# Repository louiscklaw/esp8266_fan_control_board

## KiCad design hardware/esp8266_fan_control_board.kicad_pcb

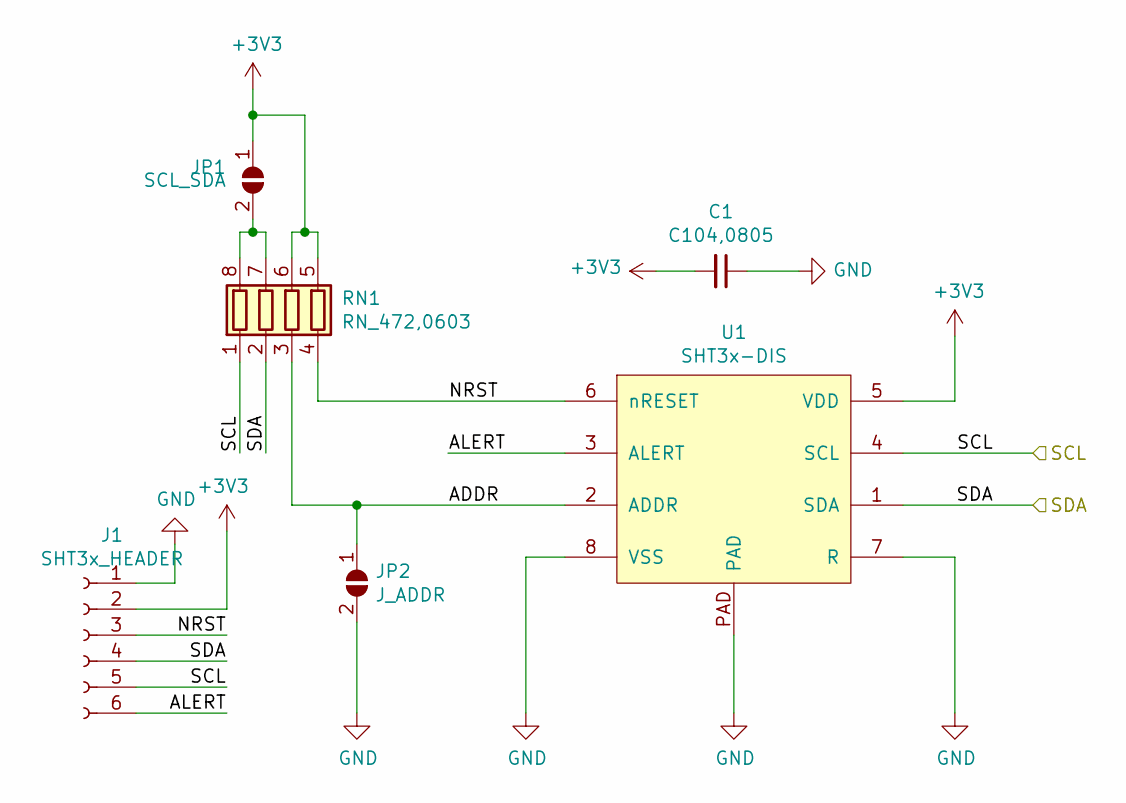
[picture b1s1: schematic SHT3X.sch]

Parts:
C1: C104,0805; C_0805_2012Metric_Pad1.15x1.40mm_HandSolder
J1: SHT3x_HEADER; PinHeader_1x06_P1.27mm_Vertical
JP1: SCL_SDA; SolderJumper-2_P1.3mm_Open_RoundedPad1.0x1.5mm
JP2: J_ADDR; SolderJumper-2_P1.3mm_Open_RoundedPad1.0x1.5mm
RN1: RN_472,0603; R_Array_Concave_4x0603
U1: SHT3x-DIS

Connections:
+3V3: C1.2, J1.2, JP1.1 (A), RN1.5 (R4.2), RN1.6 (R3.2), U1.5 (VDD); also elsewhere on the board
/SCL: J1.5, RN1.1 (R1.1), U1.4 (SCL); also elsewhere on the board
/SDA: J1.4, RN1.2 (R2.1), U1.1 (SDA); also elsewhere on the board
/SHT3X/ADDR: JP2.1 (A), RN1.3 (R3.1), U1.2 (ADDR)
/SHT3X/ALERT: J1.6, U1.3 (ALERT)
/SHT3X/NRST: J1.3, RN1.4 (R4.1), U1.6 (nRESET)
GND: C1.1, J1.1, JP2.2 (B), U1.7 (R), U1.8 (VSS), U1.PAD; also elsewhere on the board
unnamed: JP1.2 (B), RN1.7 (R2.2), RN1.8 (R1.2)

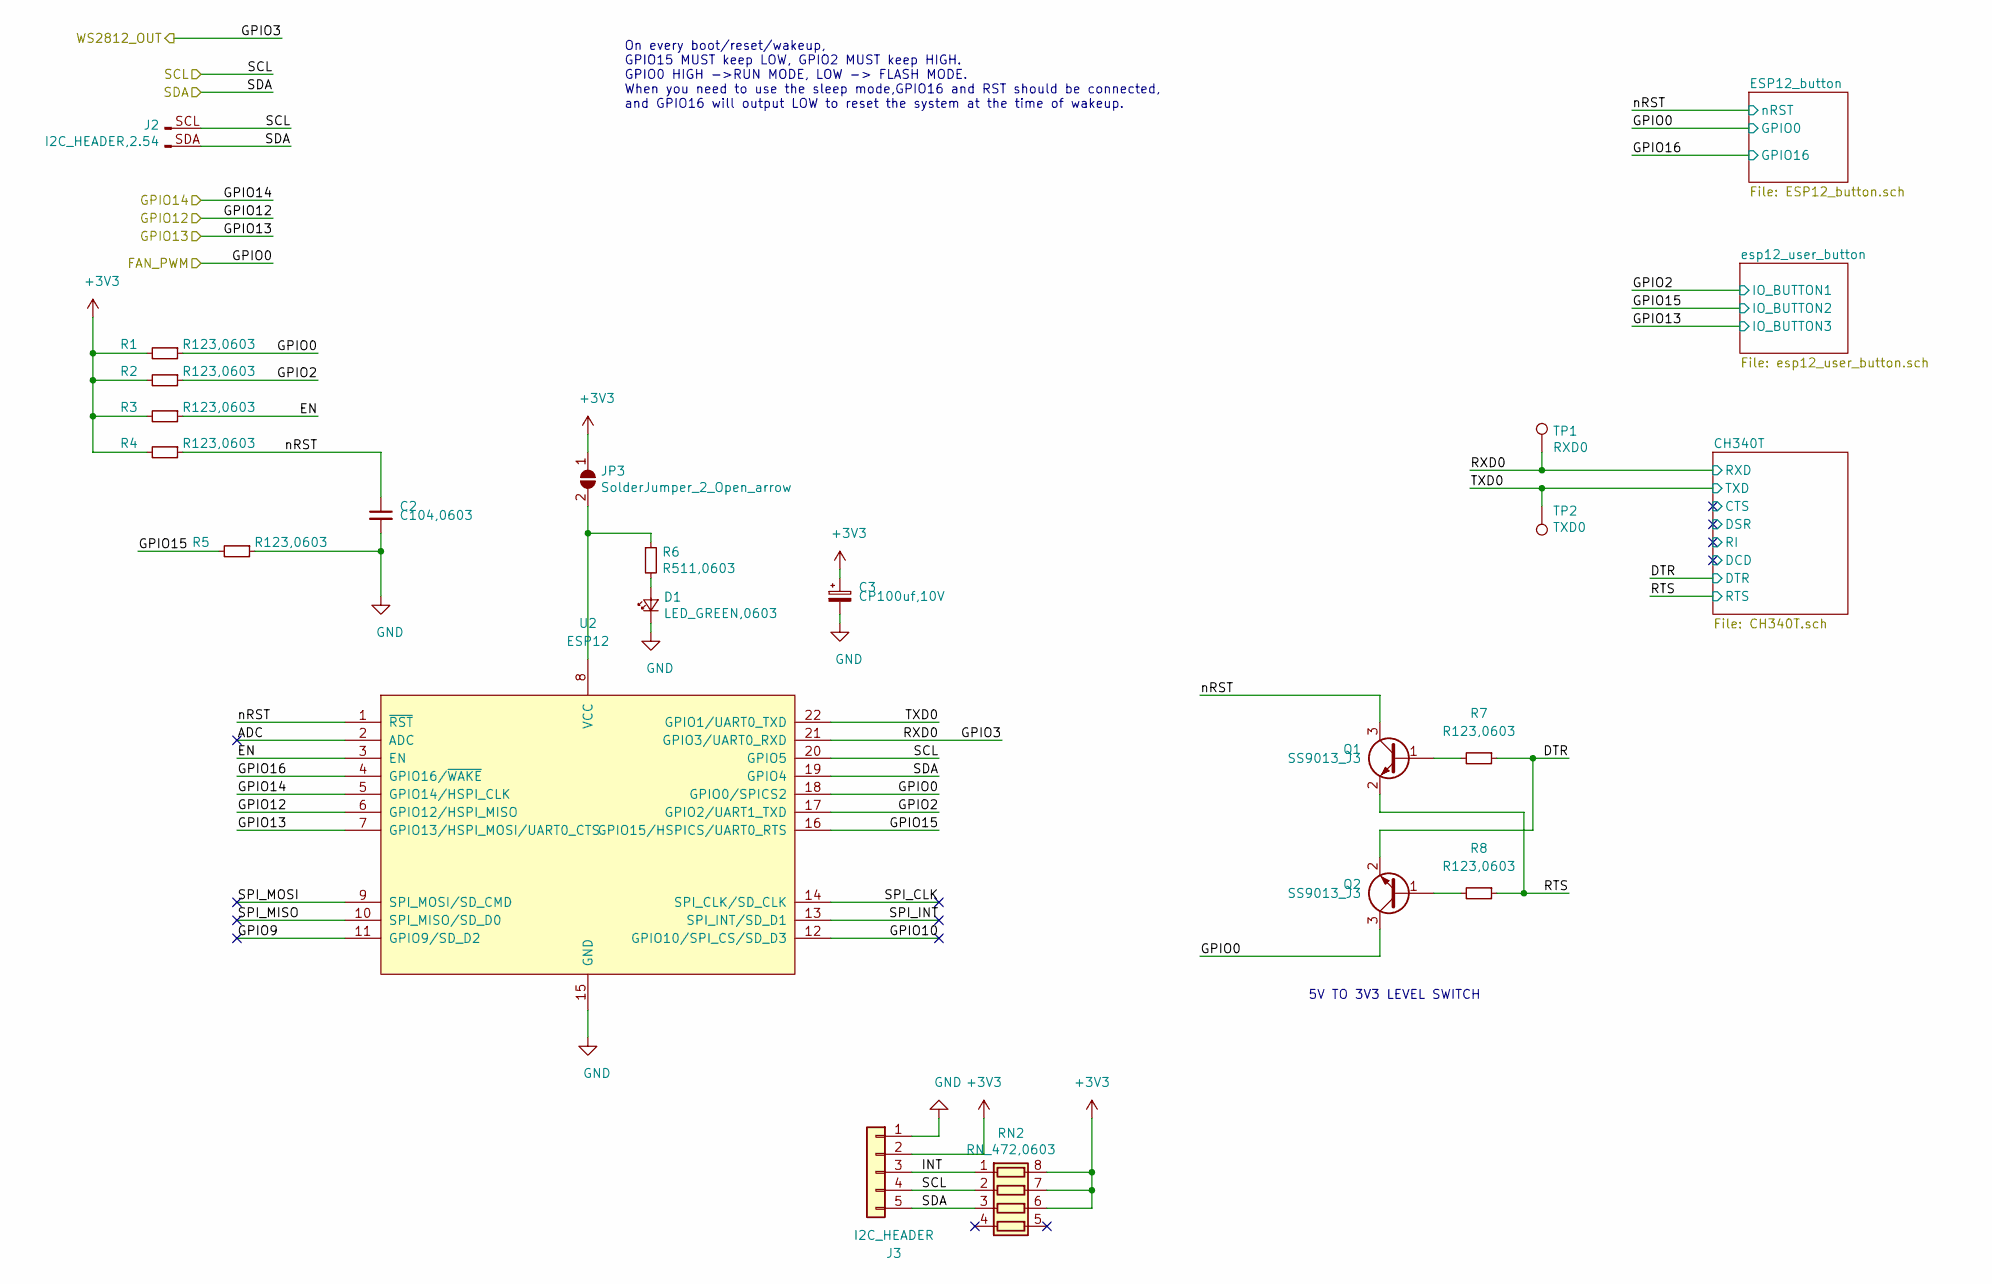
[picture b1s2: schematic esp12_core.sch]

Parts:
C2: C104,0603; C_0603_1608Metric_Pad1.05x0.95mm_HandSolder
C3: CP100uf,10V; CP_Elec_6.3x5.3
D1: LED_GREEN,0603; LED_0603_1608Metric
J2: I2C_HEADER,2.54; I2C_DEBUG,2.54
J3: I2C_HEADER; PinHeader_1x05_P2.54mm_Vertical
JP3: SolderJumper_2_Open_arrow; SolderJumper-2_P1.3mm_Open_TrianglePad1.0x1.5mm
Q1, Q2: SS9013_J3; 9013,J3,SOT23
R1, R2, R3, R4, R5, R7, R8: R123,0603; R_0603_1608Metric_Pad1.05x0.95mm_HandSolder
R6: R511,0603; R_0603_1608Metric_Pad1.05x0.95mm_HandSolder
RN2: RN_472,0603; R_Array_Concave_4x0603
TP1: RXD0; TestPoint_Pad_D1.0mm
TP2: TXD0; TestPoint_Pad_D1.0mm
U2: ESP12; ESP-12E

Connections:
+3V3: C3.1, J3.2, JP3.1 (A), R1.2, R2.2, R3.2, R4.2, RN2.6 (R3.2), RN2.7 (R2.2), RN2.8 (R1.2); also elsewhere on the board
/FAN0: Q2.3 (C), R1.1, U2.18 (GPIO0/SPICS2); also elsewhere on the board
/SCL: J2.SCL, J3.4, RN2.2 (R2.1), U2.20 (GPIO5); also elsewhere on the board
/SDA: J2.SDA, J3.5, RN2.3 (R3.1), U2.19 (GPIO4); also elsewhere on the board
/WS2812/WS2812_IN: TP1.1, U2.21 (GPIO3/UART0_RXD); also elsewhere on the board
/esp12_core/ADC: U2.2 (ADC)
/esp12_core/DTR: Q2.2 (E), R7.1; also elsewhere on the board
/esp12_core/EN: R3.1, U2.3 (EN)
/esp12_core/GPIO2: R2.1, U2.17 (GPIO2/UART1_TXD); also elsewhere on the board
/esp12_core/GPIO9: U2.11 (GPIO9/SD_D2)
/esp12_core/GPIO10: U2.12 (GPIO10/SPI_CS/SD_D3)
/esp12_core/GPIO14: U2.5 (GPIO14/HSPI_CLK); also elsewhere on the board
/esp12_core/GPIO15: R5.2, U2.16 (GPIO15/HSPICS/UART0_RTS); also elsewhere on the board
/esp12_core/GPIO16: U2.4 (GPIO16/~WAKE~); also elsewhere on the board
/esp12_core/INT: J3.3, RN2.1 (R1.1)
/esp12_core/RTS: Q1.2 (E), R8.1; also elsewhere on the board
/esp12_core/SPI_CLK: U2.14 (SPI_CLK/SD_CLK)
/esp12_core/SPI_INT: U2.13 (SPI_INT/SD_D1)
/esp12_core/SPI_MISO: U2.10 (SPI_MISO/SD_D0)
/esp12_core/SPI_MOSI: U2.9 (SPI_MOSI/SD_CMD)
/esp12_core/TXD0: TP2.1, U2.22 (GPIO1/UART0_TXD); also elsewhere on the board
/esp12_core/nRST: C2.1, Q1.3 (C), R4.1, U2.1 (~RST~); also elsewhere on the board
/rotary_encoder/A: U2.7 (GPIO13/HSPI_MOSI/UART0_CTS); also elsewhere on the board
/rotary_encoder/B: U2.6 (GPIO12/HSPI_MISO); also elsewhere on the board
GND: C2.2, C3.2, D1.1 (K), J3.1, R5.1, U2.15 (GND); also elsewhere on the board
unnamed: D1.2 (A), R6.2
unnamed: JP3.2 (B), R6.1, U2.8 (VCC)
unnamed: Q1.1 (B), R7.2
unnamed: Q2.1 (B), R8.2

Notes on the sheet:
On every boot/reset/wakeup, GPIO15 MUST keep LOW, GPIO2 MUST keep HIGH. GPIO0 HIGH ->RUN MODE, LOW -> FLASH MODE. When you need to use the sleep mode,GPIO16 and RST should be connected, and GPIO16 will output LOW to reset the system at the time of wakeup.
5V TO 3V3 LEVEL SWITCH

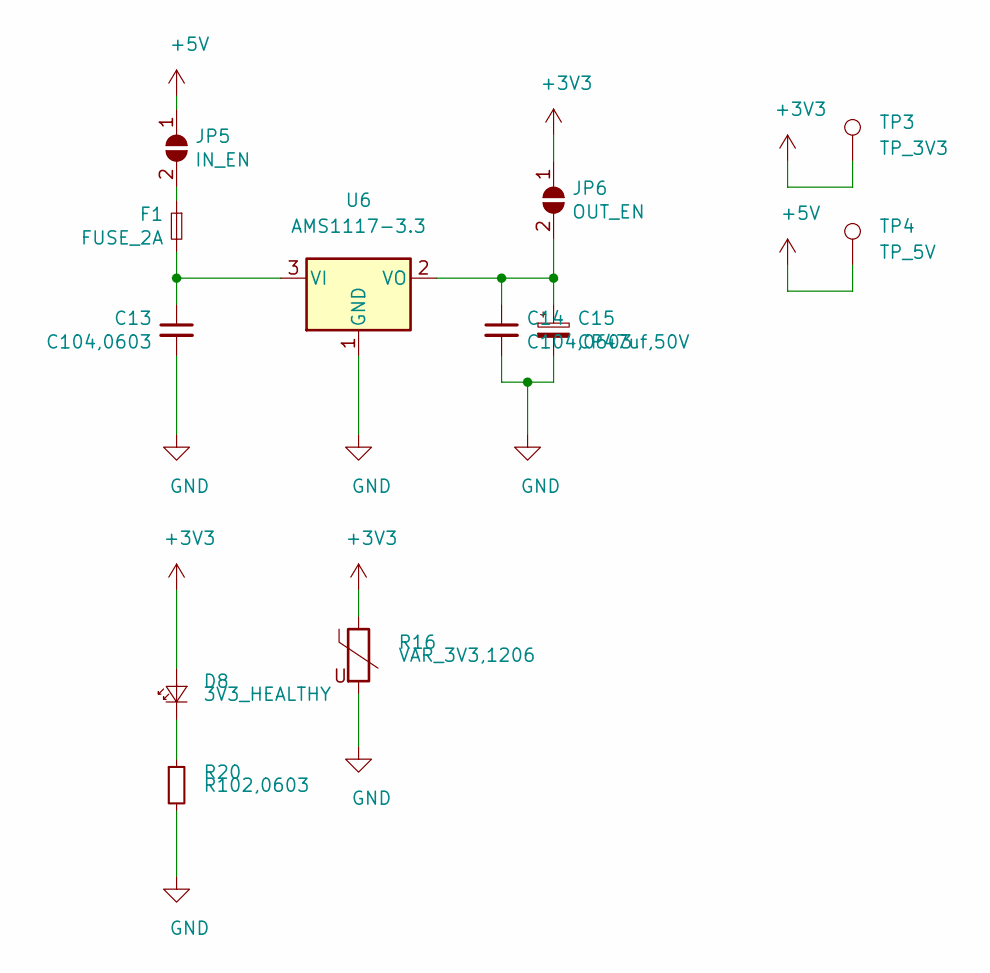
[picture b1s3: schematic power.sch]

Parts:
C13, C14: C104,0603; C_0603_1608Metric_Pad1.05x0.95mm_HandSolder
C15: CP47uf,50V; c_elec_6.3x7.7
D8: 3V3_HEALTHY; LED_0603_1608Metric_Pad1.05x0.95mm_HandSolder
F1: FUSE_2A; r_1210
JP5: IN_EN; SolderJumper-2_P1.3mm_Open_RoundedPad1.0x1.5mm
JP6: OUT_EN; SolderJumper-2_P1.3mm_Open_RoundedPad1.0x1.5mm
R16: VAR_3V3,1206; VAR_1206
R20: R102,0603; R_0603_1608Metric_Pad1.05x0.95mm_HandSolder
TP3: TP_3V3; Pin_D1.0mm_L10.0mm
TP4: TP_5V; Pin_D1.0mm_L10.0mm
U6: AMS1117-3.3; SOT-223-3_TabPin2

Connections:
+3V3: D8.2 (A), JP6.1 (A), R16.1, TP3.1; also elsewhere on the board
+5V: JP5.1 (A), TP4.1; also elsewhere on the board
GND: C13.2, C14.2, C15.2, R16.2, R20.2, U6.1 (GND); also elsewhere on the board
unnamed: C13.1, F1.2, U6.3 (VI)
unnamed: C14.1, C15.1, JP6.2 (B), U6.2 (VO)
unnamed: D8.1 (K), R20.1
unnamed: F1.1, JP5.2 (B)

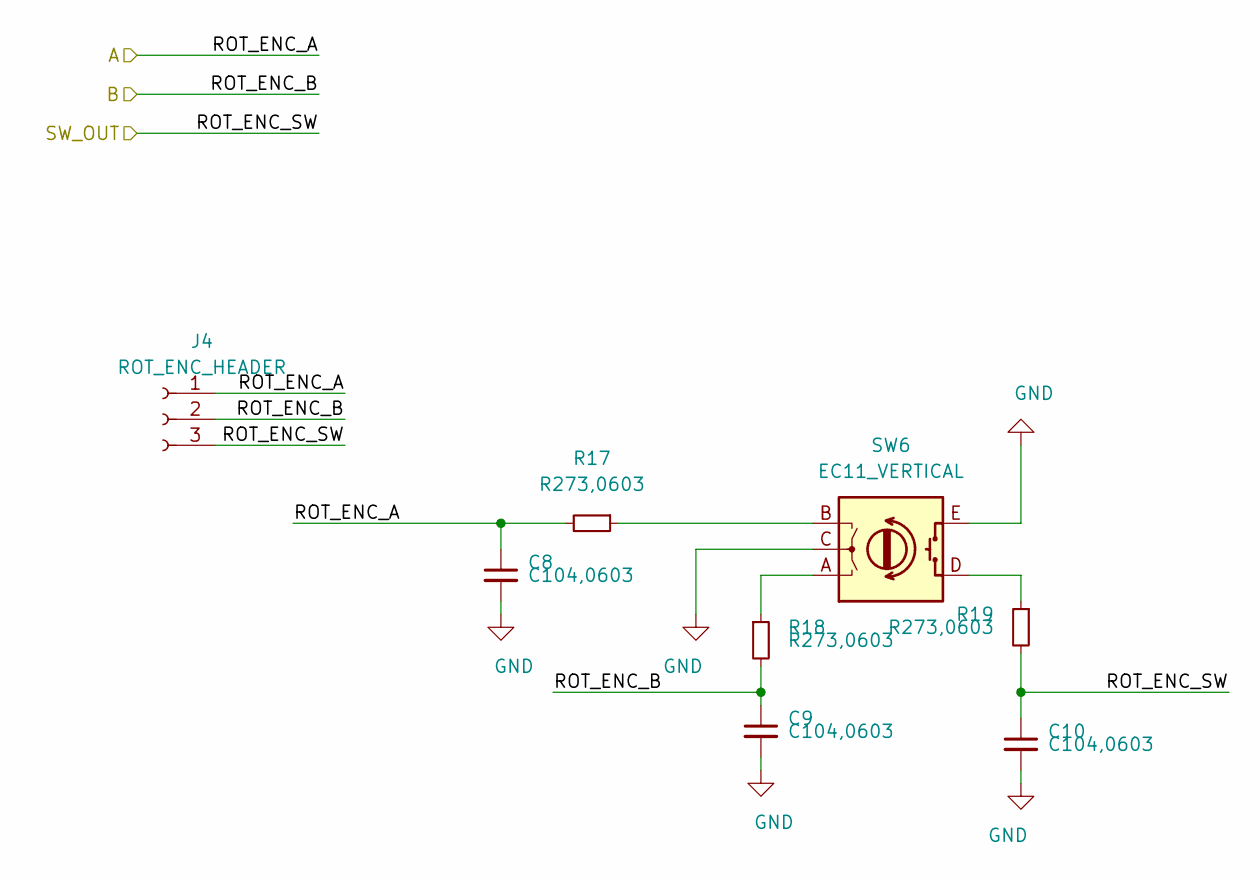
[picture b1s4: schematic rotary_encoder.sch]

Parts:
C8, C9, C10: C104,0603; C_0603_1608Metric_Pad1.05x0.95mm_HandSolder
J4: ROT_ENC_HEADER; PinHeader_1x03_P1.27mm_Vertical
R17, R18, R19: R273,0603; R_0603_1608Metric_Pad1.05x0.95mm_HandSolder
SW6: EC11_VERTICAL; RotaryEncoder_Alps_EC11E_Vertical_H20mm

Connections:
/esp12_core/GPIO14: C10.1, J4.3, R19.2; also elsewhere on the board
/rotary_encoder/A: C8.1, J4.1, R17.2; also elsewhere on the board
/rotary_encoder/B: C9.1, J4.2, R18.2; also elsewhere on the board
GND: C8.2, C9.2, C10.2, SW6.C, SW6.E; also elsewhere on the board
unnamed: R17.1, SW6.B
unnamed: R18.1, SW6.A
unnamed: R19.1, SW6.D

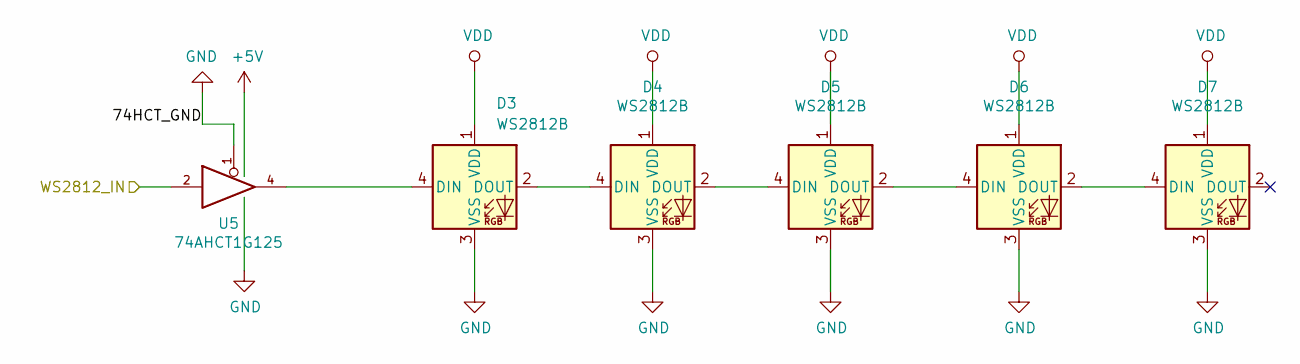
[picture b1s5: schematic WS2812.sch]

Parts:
D3, D4, D5, D6, D7: WS2812B; LED_WS2812B_5050_white
U5: 74AHCT1G125; SOT-23-5_HandSoldering

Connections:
+5V: U5.5 (VCC); also elsewhere on the board
/WS2812/WS2812_IN: U5.2; also elsewhere on the board
GND: D3.3 (VSS), D4.3 (VSS), D5.3 (VSS), D6.3 (VSS), D7.3 (VSS), U5.1, U5.3 (GND); also elsewhere on the board
unnamed: D3.2 (DOUT), D4.4 (DIN)
unnamed: D3.4 (DIN), U5.4
unnamed: D4.2 (DOUT), D5.4 (DIN)
unnamed: D5.2 (DOUT), D6.4 (DIN)
unnamed: D6.2 (DOUT), D7.4 (DIN)
VDD: D3.1 (VDD), D4.1 (VDD), D5.1 (VDD), D6.1 (VDD), D7.1 (VDD)

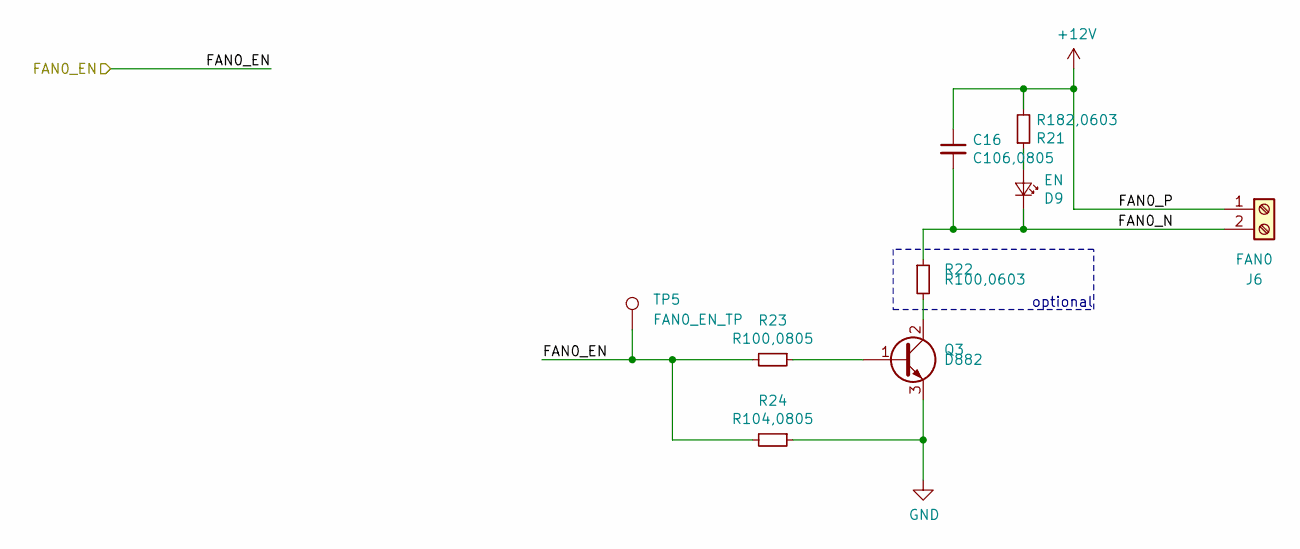
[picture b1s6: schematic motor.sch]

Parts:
C16: C106,0805; C_0805_2012Metric_Pad1.15x1.40mm_HandSolder
D9: EN; LED_0603_1608Metric_Pad1.05x0.95mm_HandSolder
J6: FAN0; XH_TEMPERATURE_SENSOR_TERMINAL_2.54
Q3: D882; SOT-89-3,thermal_vias
R21: R182,0603; R_0603_1608Metric_Pad1.05x0.95mm_HandSolder
R22: R100,0603; R_0603_1608Metric_Pad1.05x0.95mm_HandSolder
R23: R100,0805; R_0805_2012Metric_Pad1.15x1.40mm_HandSolder
R24: R104,0805; R_0805_2012Metric_Pad1.15x1.40mm_HandSolder
TP5: FAN0_EN_TP; PinHeader_1x01_P1.00mm_Vertical

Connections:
+12V: C16.1, J6.1, R21.2
/FAN0: R23.2, R24.2, TP5.1; also elsewhere on the board
/motor/FAN0_N: C16.2, D9.1 (K), J6.2, R22.1
GND: Q3.3 (E), R24.1; also elsewhere on the board
unnamed: D9.2 (A), R21.1
unnamed: Q3.1 (B), R23.1
unnamed: Q3.2 (C), R22.2

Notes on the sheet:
optional

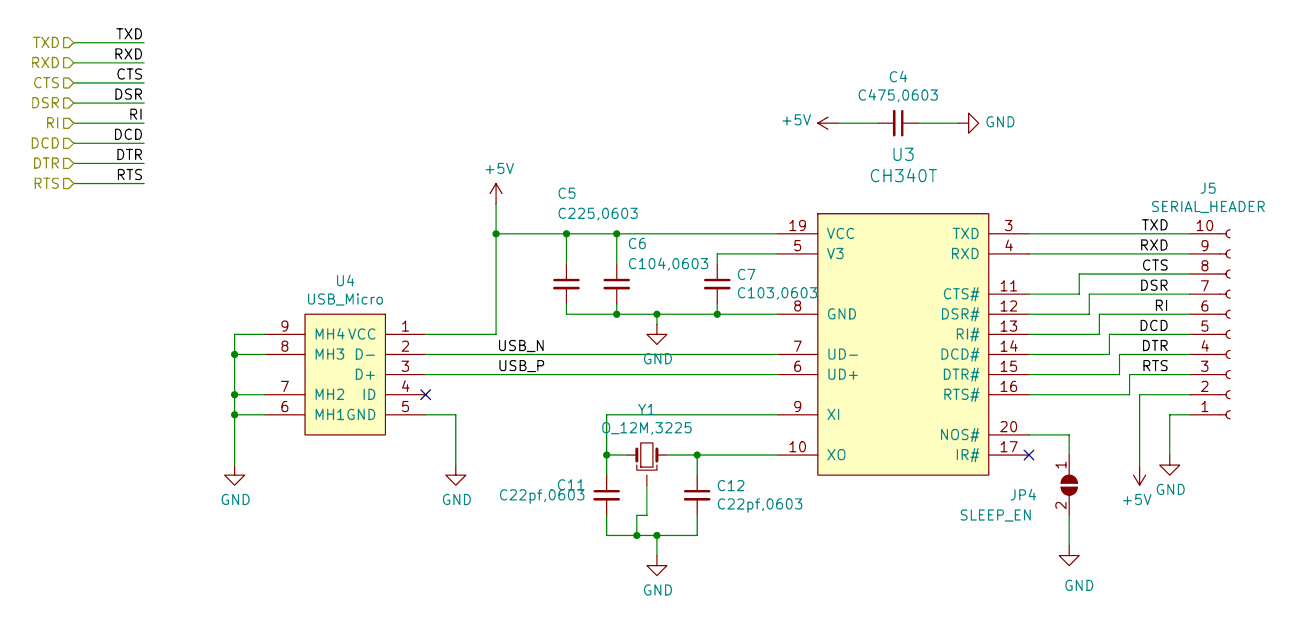
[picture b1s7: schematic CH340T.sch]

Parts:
C4: C475,0603; C_0603_1608Metric_Pad1.05x0.95mm_HandSolder
C5: C225,0603; C_0603_1608Metric_Pad1.05x0.95mm_HandSolder
C6: C104,0603; C_0603_1608Metric_Pad1.05x0.95mm_HandSolder
C7: C103,0603; C_0603_1608Metric_Pad1.05x0.95mm_HandSolder
C11, C12: C22pf,0603; C_0603_1608Metric_Pad1.05x0.95mm_HandSolder
J5: SERIAL_HEADER; PinHeader_1x10_P1.27mm_Vertical
JP4: SLEEP_EN; SolderJumper-2_P1.3mm_Open_RoundedPad1.0x1.5mm
U3: CH340T; CH340T_SSOP-20
U4: USB_Micro; USB_Micro-B_Molex-105017-0001
Y1: O_12M,3225; OSC_3225

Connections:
+5V: C4.2, C5.1, C6.1, J5.2, U3.19 (VCC), U4.1 (VCC); also elsewhere on the board
/WS2812/WS2812_IN: J5.9, U3.4 (RXD); also elsewhere on the board
/esp12_core/CH340T/CTS: J5.8, U3.11 (CTS#)
/esp12_core/CH340T/DCD: J5.5, U3.14 (DCD#)
/esp12_core/CH340T/DSR: J5.7, U3.12 (DSR#)
/esp12_core/CH340T/RI: J5.6, U3.13 (RI#)
/esp12_core/CH340T/USB_N: U3.7 (UD-), U4.2 (D-)
/esp12_core/CH340T/USB_P: U3.6 (UD+), U4.3 (D+)
/esp12_core/DTR: J5.4, U3.15 (DTR#); also elsewhere on the board
/esp12_core/RTS: J5.3, U3.16 (RTS#); also elsewhere on the board
/esp12_core/TXD0: J5.10, U3.3 (TXD); also elsewhere on the board
GND: C4.1, C5.2, C6.2, C7.2, C11.2, C12.2, J5.1, JP4.2 (B), U3.8 (GND), U4.5 (GND), U4.6 (MH1), U4.7 (MH2), U4.8 (MH3), U4.9 (MH4), Y1.2; also elsewhere on the board
unnamed: C7.1, U3.5 (V3)
unnamed: C11.1, U3.9 (XI), Y1.1
unnamed: C12.1, U3.10 (XO), Y1.3
unnamed: JP4.1 (A), U3.20 (NOS#)

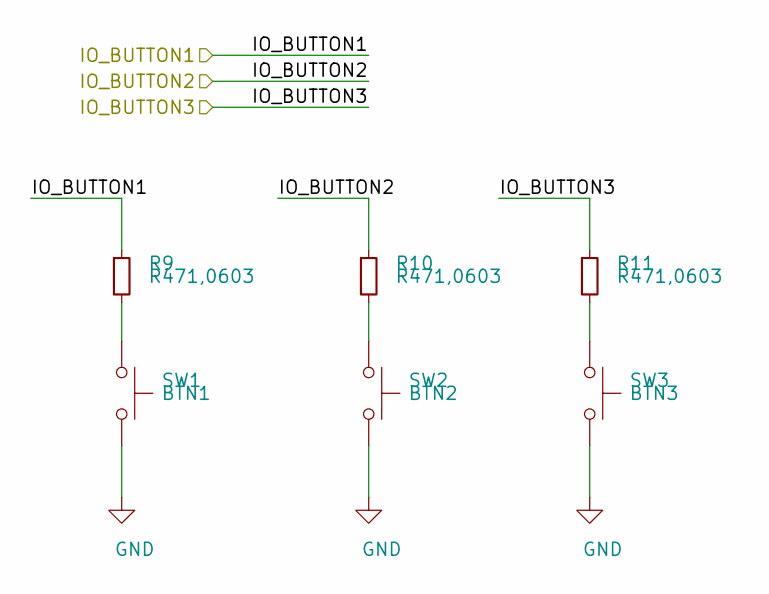
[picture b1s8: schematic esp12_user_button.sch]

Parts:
R9, R10, R11: R471,0603; R_0603_1608Metric_Pad1.05x0.95mm_HandSolder
SW1: BTN1; SW_SPST_CK_RS282G05A3
SW2: BTN2; SW_SPST_CK_RS282G05A3
SW3: BTN3; SW_SPST_CK_RS282G05A3

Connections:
/esp12_core/GPIO2: R9.1; also elsewhere on the board
/esp12_core/GPIO15: R10.1; also elsewhere on the board
/rotary_encoder/A: R11.1; also elsewhere on the board
GND: SW1.2, SW2.2, SW3.2; also elsewhere on the board
unnamed: R9.2, SW1.1
unnamed: R10.2, SW2.1
unnamed: R11.2, SW3.1

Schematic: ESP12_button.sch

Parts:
D2: LED_BLUE,0603; LED_0603_1608Metric_Pad1.05x0.95mm_HandSolder
R12, R13, R15: R471,0603; R_0603_1608Metric_Pad1.05x0.95mm_HandSolder
R14: R0,0603; R_0603_1608Metric_Pad1.05x0.95mm_HandSolder
SW4: FLASH; SW_SPST_CK_RS282G05A3
SW5: RST; SW_SPST_CK_RS282G05A3

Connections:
+3V3: R12.1; also elsewhere on the board
/FAN0: R13.1; also elsewhere on the board
/esp12_core/GPIO16: D2.1 (K), R14.1; also elsewhere on the board
/esp12_core/nRST: R15.1; also elsewhere on the board
GND: SW4.2, SW5.2; also elsewhere on the board
unnamed: D2.2 (A), R12.2
unnamed: R13.2, SW4.1
unnamed: R14.2, R15.2, SW5.1

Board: 2 copper layers, 85 parts (0 on the bottom side), 61 nets, no tracks yet.

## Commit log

2019-06-20 update,
2019-06-20 init gitignore,
2019-06-23 update to remove bak files,
2019-06-23 update to delete cp2102,
2020-05-05 ci: init travis build config,
2020-05-05 ci: init travis token,
